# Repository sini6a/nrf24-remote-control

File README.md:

# nRF24-Based Remote Control

A complete 2.4 GHz wireless remote control system. The PCBs and firmware are tested and working. The first PCB revision required soldering external wires for programming — this was fixed with an updated programming header in the current revision.

## Repository Layout

```
Firmware/
  nrf24le1-transmitter/   # Transmitter firmware (SDCC / nRF24LE1)
  nrf52820-receiver/      # Receiver firmware (CMake / nRF52820)
KiCad/
  nrf24le1-transmitter/   # Transmitter PCB design
  nrf52820-receiver/      # Receiver PCB design
```

## Transmitter

The transmitter is based on the **nRF24LE1**, which uses Nordic's proprietary 2.4 GHz **ShockBurst** protocol. This chip operates at **1.9 V – 3.6 V**, making it ideal for **two AAA batteries**.

### Features
- **15 buttons** — two positioned on the PCB sides for experimentation
- **Antenna** — top-mounted PCB trace antenna for improved signal
- **Programming** — SPI + PROG pin, flashable via Arduino; pinout printed on board

See [Firmware/nrf24le1-transmitter/README.md](Firmware/nrf24le1-transmitter/README.md) and [FLASHING_GUIDE.md](Firmware/nrf24le1-transmitter/FLASHING_GUIDE.md).

## Receiver

The receiver is based on the **nRF52820**, the most cost-effective Nordic chip with native **USB HID** support. It is an ARM Cortex-M4 microcontroller programmed over **SWD**.

### Features
- **USB HID** — exposes keyboard and consumer-control interfaces to the host
- **Programming** — TagConnect 6-pin NL connector (SWD)
- **Hardware** — PCB trace antenna and PCB-mount USB 2.0 connector

See [Firmware/nrf52820-receiver/README.md](Firmware/nrf52820-receiver/README.md) and [FLASHING_GUIDE.md](Firmware/nrf52820-receiver/FLASHING_GUIDE.md).

## Status

- [x] Program the remote
- [x] Program the receiver
- [x] Test stability and antenna performance
- [x] Design a 3D-printed case

## Acknowledgements

- [Dean Cording](https://github.com/DeanCording/nRF24LE1_SDK) — nRF24LE1 SDK used by the transmitter firmware
- [polkabana](https://github.com/polkabana/nRF24LE1_Programmer) — nRF24LE1 Programmer utility used for flashing the transmitter
- [greenlsi](https://github.com/greenlsi/nrf5-sdk/) — nRF5 SDK used by the receiver firmware

## Contribution

Contributions are welcome! Please open an issue first to discuss your proposed changes before submitting a pull request.

## Support

If you find this project useful, you can buy me a coffee:

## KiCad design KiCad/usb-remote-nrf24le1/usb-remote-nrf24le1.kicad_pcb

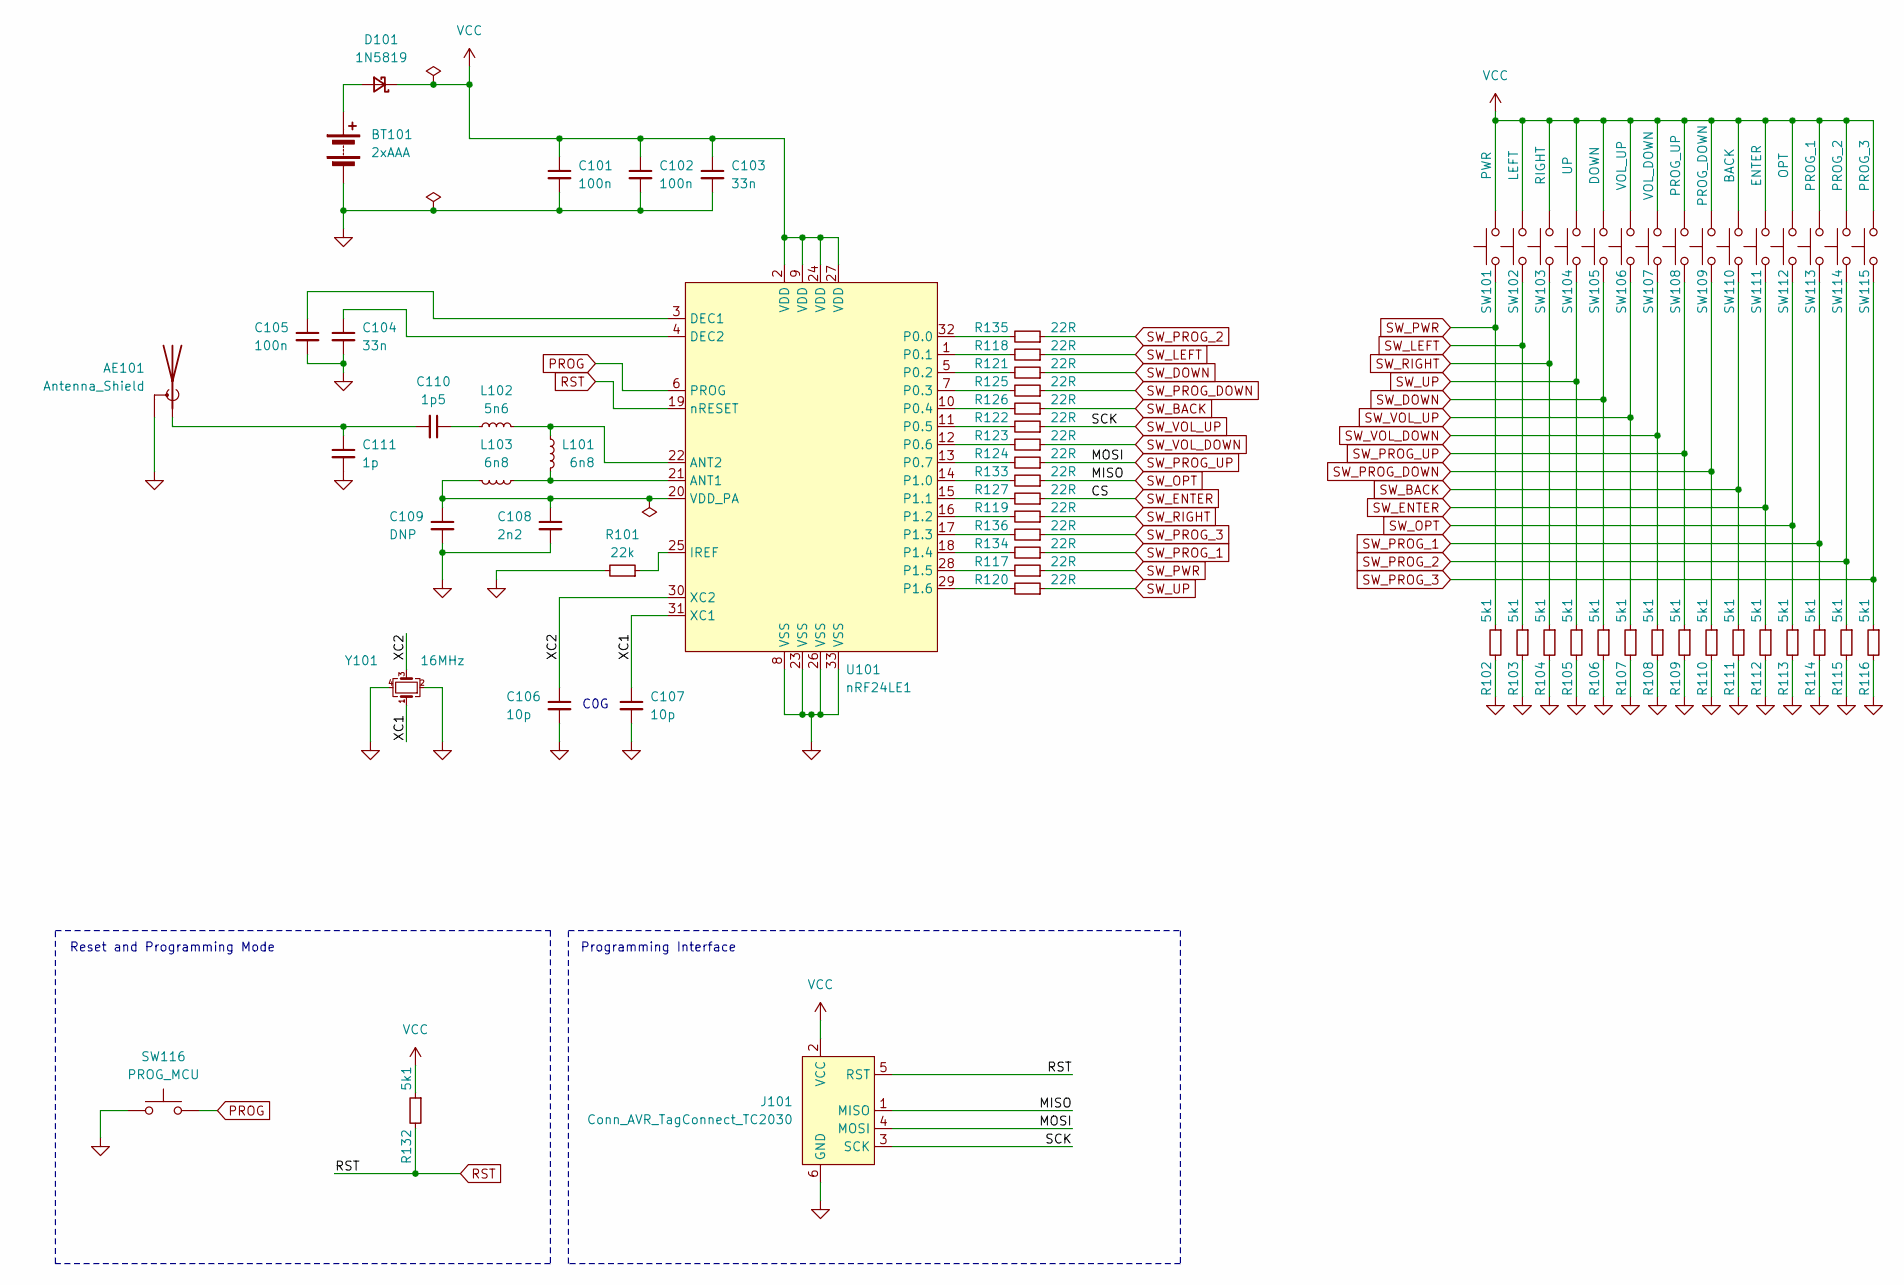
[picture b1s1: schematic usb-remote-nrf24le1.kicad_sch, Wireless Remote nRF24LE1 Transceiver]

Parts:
AE101: Antenna_Shield; Texas_SWRA117D_2.4GHz_Right
BT101: 2xAAA; BatteryHolder_Keystone_2468_2xAAA
C101, C102, C105: 100n; C_0402_1005Metric; MPN C1525
C103, C104: 33n; C_0603_1608Metric; MPN C21117
C106, C107: 10p; C_0402_1005Metric; MPN C32949
C108: 2n2; C_0402_1005Metric; MPN C84703
C109: DNP; C_0402_1005Metric
C110: 1p5; C_0402_1005Metric; MPN C76900
C111: 1p; C_0402_1005Metric; MPN C72134
D101: 1N5819; D_SMA; MPN C2480
J101: Conn_AVR_TagConnect_TC2030; Tag-Connect_TC2030-IDC-NL_2x03_P1.27mm_Vertical
L101, L103: 6n8; L_0402_1005Metric; MPN C77110
L102: 5n6; L_0402_1005Metric; MPN C85670
R101: 22k; R_0402_1005Metric; MPN C25768
R102, R103, R104, R105, R106, R107, R108, R109, R110, R111, R112, R113, R114, R115, R116, R132: 5k1; R_0402_1005Metric; MPN C25905
R117, R118, R119, R120, R121, R122, R123, R124, R125, R126, R127, R133, R134, R135, R136: 22R; R_0402_1005Metric; MPN C25092
SW101: PWR; SW_PUSH_6mm_H4.3mm
SW102: LEFT; SW_PUSH_6mm_H4.3mm
SW103: RIGHT; SW_PUSH_6mm_H4.3mm
SW104: UP; SW_PUSH_6mm_H4.3mm
SW105: DOWN; SW_PUSH_6mm_H4.3mm
SW106: VOL_UP; SW_PUSH_6mm_H4.3mm
SW107: VOL_DOWN; SW_PUSH_6mm_H4.3mm
SW108: PROG_UP; SW_PUSH_6mm_H4.3mm
SW109: PROG_DOWN; SW_PUSH_6mm_H4.3mm
SW110: BACK; SW_PUSH_6mm_H4.3mm
SW111: ENTER; SW_PUSH_6mm_H4.3mm
SW112: OPT; SW_PUSH_6mm_H4.3mm
SW113: PROG_1; SW_PUSH_6mm_H4.3mm
SW114: PROG_2; SW_Tactile_SPST_Angled_PTS645Vx31-2LFS
SW115: PROG_3; SW_Tactile_SPST_Angled_PTS645Vx31-2LFS
SW116: PROG_MCU; SW_Push_1P1T_XKB_TS-1187A; MPN C318884
U101: nRF24LE1; QFN-32-1EP_5x5mm_P0.5mm_EP3.6x3.6mm_ThermalVias; MPN C18315
Y101: 16MHz; Crystal_SMD_3225-4Pin_3.2x2.5mm; MPN C13738

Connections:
/XC1: C107.1, U101.31 (XC1), Y101.1
/XC2: C106.1, U101.30 (XC2), Y101.3
GND: AE101.2 (Shield), BT101.2 (-), C101.2, C102.2, C103.2, C104.2, C105.2, C106.2, C107.2, C108.2, C109.2, C111.2, J101.6 (GND), R101.2, R102.2, R103.2, R104.2, R105.2, R106.2, R107.2, R108.2, R109.2, R110.2, R111.2, R112.2, R113.2, R114.2, R115.2, R116.2, SW116.1, U101.8 (VSS), U101.23 (VSS), U101.26 (VSS), U101.33 (VSS), Y101.2, Y101.4
unnamed: AE101.1 (A), C110.2, C111.1
unnamed: BT101.1 (+), D101.2 (A)
unnamed: C110.1, L102.2
unnamed: L101.1, L103.2, U101.21 (ANT1)
unnamed: L101.2, L102.1, U101.22 (ANT2)
unnamed: C105.1, U101.3 (DEC1)
unnamed: C104.1, U101.4 (DEC2)
unnamed: R101.1, U101.25 (IREF)
unnamed: R135.2, U101.32 (P0.0)
unnamed: R118.2, U101.1 (P0.1)
unnamed: R121.2, U101.5 (P0.2)
unnamed: R125.2, U101.7 (P0.3)
unnamed: R126.2, U101.10 (P0.4)
unnamed: R122.2, U101.11 (P0.5)
unnamed: R123.2, U101.12 (P0.6)
unnamed: R124.2, U101.13 (P0.7)
unnamed: R133.2, U101.14 (P1.0)
unnamed: R127.2, U101.15 (P1.1)
unnamed: R119.2, U101.16 (P1.2)
unnamed: R136.2, U101.17 (P1.3)
unnamed: R134.2, U101.18 (P1.4)
unnamed: R117.2, U101.28 (P1.5)
unnamed: R120.2, U101.29 (P1.6)
unnamed: C108.1, C109.1, L103.1, U101.20 (VDD_PA)
PROG: SW116.2, U101.6 (PROG)
RST: J101.5 (RST), R132.2, U101.19 (nRESET)
SW_BACK: R111.1, R126.1, SW110.1
SW_DOWN: R106.1, R121.1, SW105.1
SW_ENTER: R112.1, R127.1, SW111.1
SW_LEFT: R103.1, R118.1, SW102.1
SW_OPT: J101.1 (MISO), R113.1, R133.1, SW112.1
SW_PROG_1: R114.1, R134.1, SW113.1
SW_PROG_2: R115.1, R135.1, SW114.1
SW_PROG_3: R116.1, R136.1, SW115.1
SW_PROG_DOWN: R110.1, R125.1, SW109.1
SW_PROG_UP: J101.4 (MOSI), R109.1, R124.1, SW108.1
SW_PWR: R102.1, R117.1, SW101.1
SW_RIGHT: R104.1, R119.1, SW103.1
SW_UP: R105.1, R120.1, SW104.1
SW_VOL_DOWN: R108.1, R123.1, SW107.1
SW_VOL_UP: J101.3 (SCK), R107.1, R122.1, SW106.1
VCC: C101.1, C102.1, C103.1, D101.1 (K), J101.2 (VCC), R132.1, SW101.2, SW102.2, SW103.2, SW104.2, SW105.2, SW106.2, SW107.2, SW108.2, SW109.2, SW110.2, SW111.2, SW112.2, SW113.2, SW114.2, SW115.2, U101.2 (VDD), U101.9 (VDD), U101.24 (VDD), U101.27 (VDD)

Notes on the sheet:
C0G
Programming Interface
Reset and Programming Mode

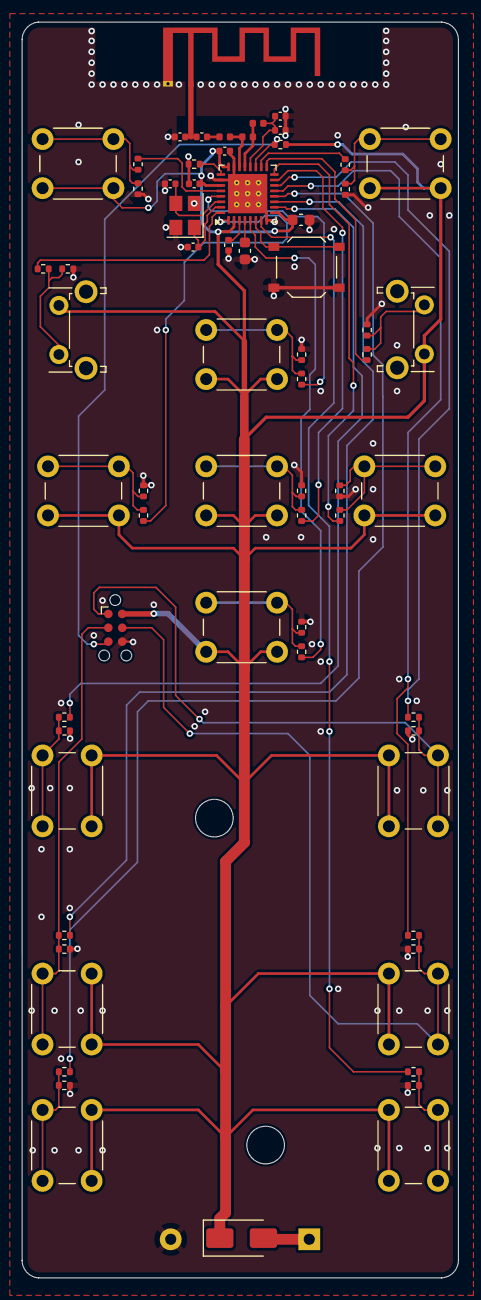
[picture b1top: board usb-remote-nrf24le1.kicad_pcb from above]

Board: 2 copper layers, 40.0 x 115.1 mm, 68 parts (1 on the bottom side), 45 nets.

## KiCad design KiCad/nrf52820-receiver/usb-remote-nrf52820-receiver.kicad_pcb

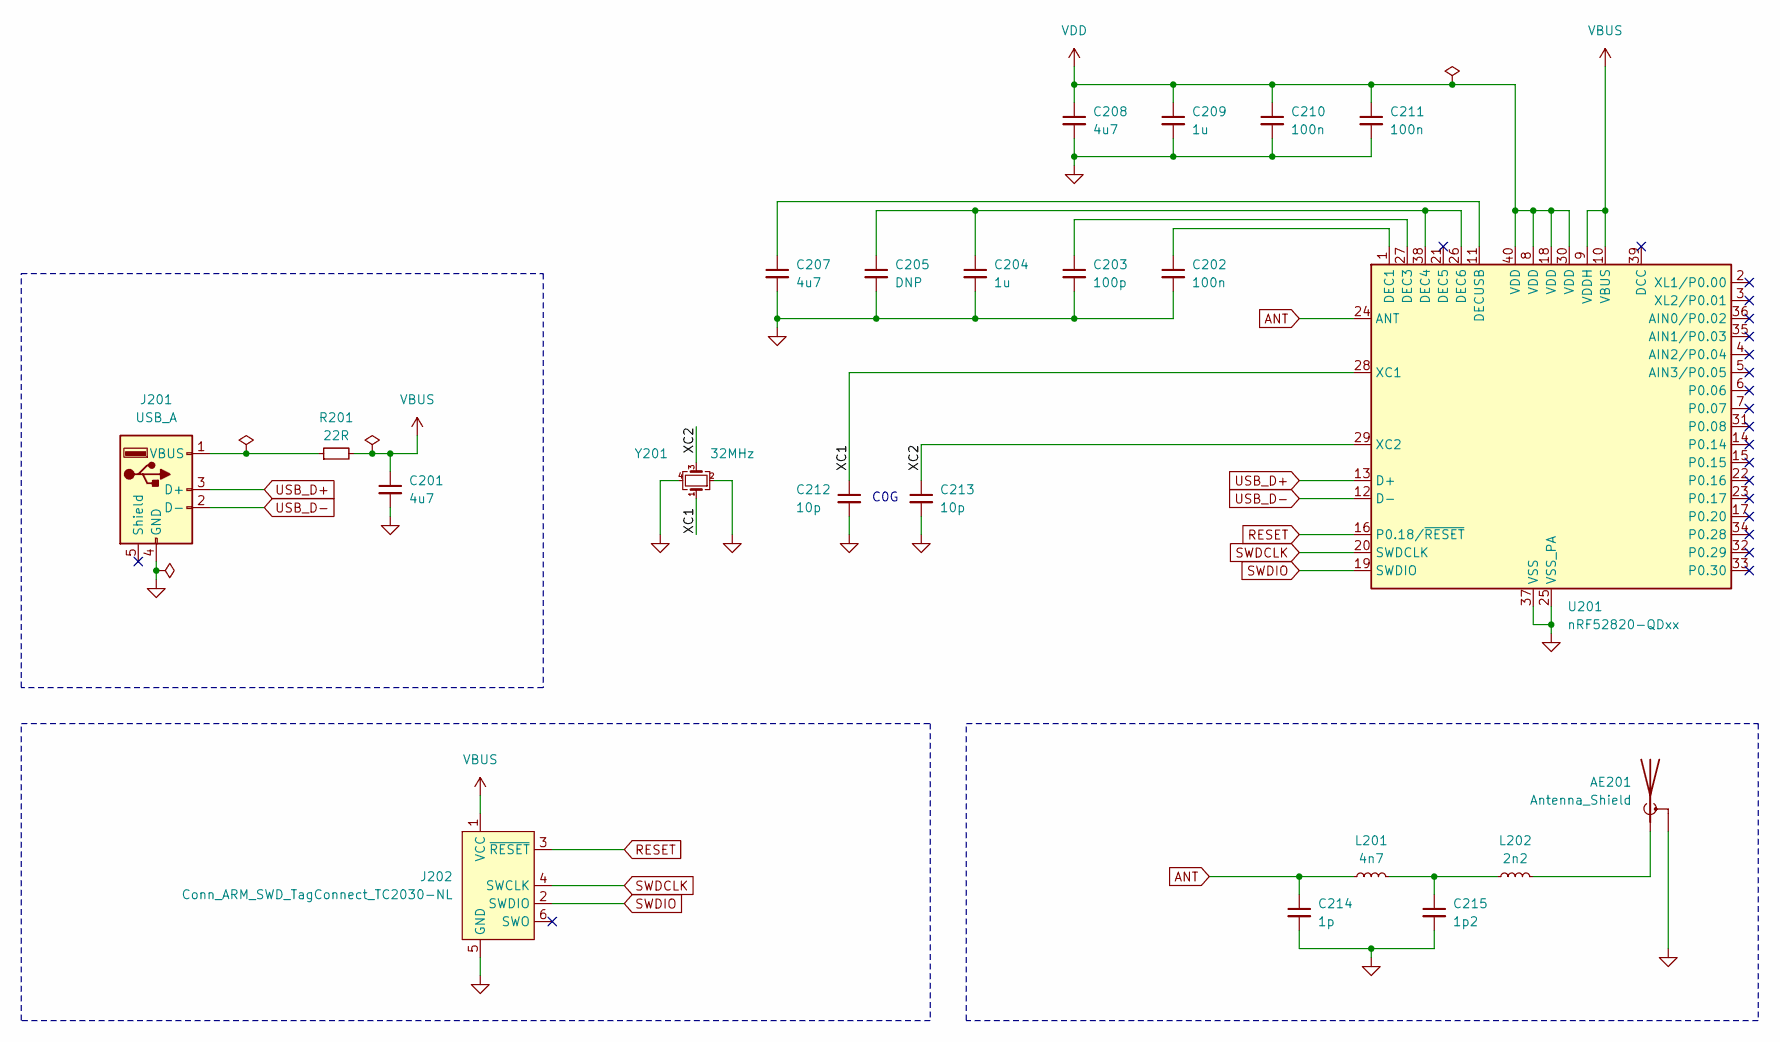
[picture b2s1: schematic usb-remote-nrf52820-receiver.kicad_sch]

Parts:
AE201: Antenna_Shield; Texas_SWRA117D_2.4GHz_Right
C201, C207, C208: 4u7; C_0603_1608Metric; MPN C19666
C202, C210, C211: 100n; C_0402_1005Metric; MPN C1525
C203: 100p; C_0402_1005Metric; MPN C1546
C204, C209: 1u; C_0402_1005Metric; MPN C52923
C205: DNP; C_0402_1005Metric
C212, C213: 10p; C_0402_1005Metric; MPN C32949
C214: 1p; C_0402_1005Metric; MPN C72134
C215: 1p2; C_0402_1005Metric; MPN C76899
J201: USB_A; PCB_USB_2.0
J202: Conn_ARM_SWD_TagConnect_TC2030-NL; Tag-Connect_TC2030-IDC-NL_2x03_P1.27mm_Vertical
L201: 4n7; L_0402_1005Metric; MPN C86065
L202: 2n2; L_0402_1005Metric; MPN C86061
R201: 22R; C_0402_1005Metric; MPN C25092
U201: nRF52820-QDxx; QFN-40-1EP_5x5mm_P0.4mm_EP3.6x3.6mm; MPN C3015612
Y201: 32MHz; Crystal_SMD_2016-4Pin_2.0x1.6mm; MPN C2901738

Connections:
/XC1: C212.1, U201.28 (XC1), Y201.1
/XC2: C213.1, U201.29 (XC2), Y201.3
ANT: C214.1, L201.1, U201.24 (ANT)
GND: AE201.2 (Shield), C201.2, C202.2, C203.2, C204.2, C205.2, C207.2, C208.2, C209.2, C210.2, C211.2, C212.2, C213.2, C214.2, C215.2, J201.4 (GND), J202.5 (GND), U201.25 (VSS_PA), U201.37 (VSS), U201.41 (VSS), Y201.2, Y201.4
unnamed: AE201.1 (A), L202.2
unnamed: C215.1, L201.2, L202.1
unnamed: J201.1 (VBUS), R201.1
unnamed: C202.1, U201.1 (DEC1)
unnamed: C203.1, U201.27 (DEC3)
unnamed: C204.1, C205.1, U201.26 (DEC6), U201.38 (DEC4)
unnamed: C207.1, U201.11 (DECUSB)
RESET: J202.3 (~RESET), U201.16 (P0.18/~RESET)
SWDCLK: J202.4 (SWCLK), U201.20 (SWDCLK)
SWDIO: J202.2 (SWDIO), U201.19 (SWDIO)
USB_D+: J201.3 (D+), U201.13 (D+)
USB_D-: J201.2 (D-), U201.12 (D-)
VBUS: C201.1, J202.1 (VCC), R201.2, U201.9 (VDDH), U201.10 (VBUS)
VDD: C208.1, C209.1, C210.1, C211.1, U201.8 (VDD), U201.18 (VDD), U201.30 (VDD), U201.40 (VDD)

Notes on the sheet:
C0G

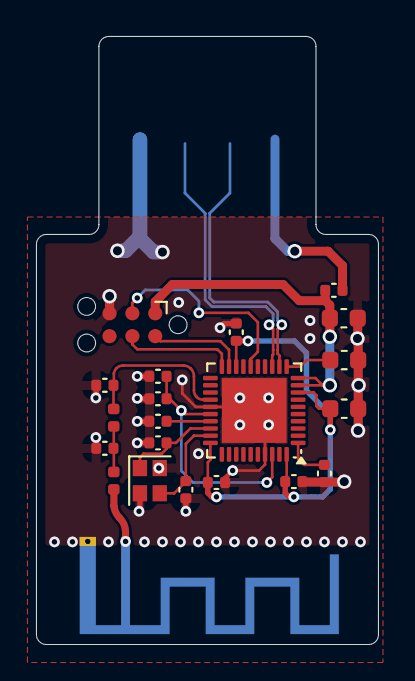
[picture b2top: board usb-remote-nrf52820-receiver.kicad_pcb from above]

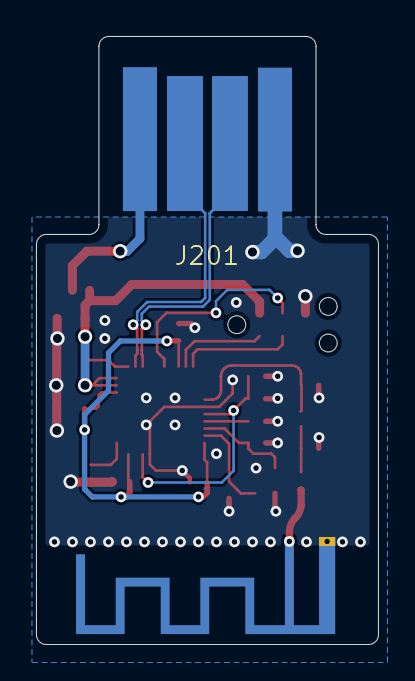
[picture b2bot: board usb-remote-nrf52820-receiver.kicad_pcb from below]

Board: 2 copper layers, 19.0 x 33.8 mm, 22 parts (2 on the bottom side), 18 nets.

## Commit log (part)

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2026-04-14 redesigned programming header and routing cleanup
2026-04-18 added remote firmware
2026-04-18 add receiver firmware
2026-04-18 added dependencies and cleanup
2026-04-18 updated guides and readme
2026-04-18 added missing module
2026-04-18 updated nrf5-sdk reference
2026-06-30 add image
2026-06-30 Add image to README for visual enhancement
    Added an image to the README for better visual representation.
